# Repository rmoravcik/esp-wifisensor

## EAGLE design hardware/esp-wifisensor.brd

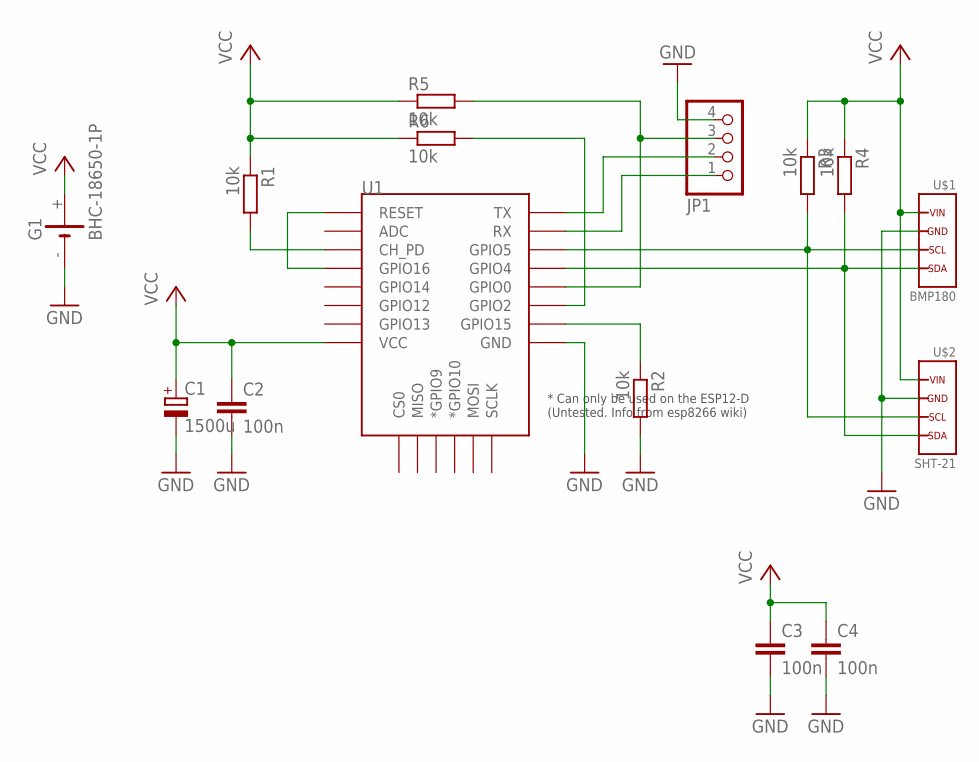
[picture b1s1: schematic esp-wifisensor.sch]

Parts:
C1: 1500u; E5-13
C2, C3, C4: 100n; C1206K
G1: BHC-18650-1P
JP1: PINHD-1X4; 1X04
R1, R2, R3, R4, R5, R6: 10k; M1206
U1: ESP12ESMD; ESP12E-SMD
U$1: BMP180
U$2: SHT-21

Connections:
GND: C1.-, C2.2, C3.2, C4.2, G1.-, JP1.4, R2.2, U1.GND, U$1.GND, U$2.GND
unnamed: U1.GPIO16, U1.RESET
unnamed: R3.2, U1.GPIO5, U$1.SCL, U$2.SCL
unnamed: R4.2, U1.GPIO4, U$1.SDA, U$2.SDA
unnamed: R2.1, U1.GPIO15
unnamed: JP1.3, R5.2, U1.GPIO0
unnamed: R1.2, U1.CH_PD
unnamed: R6.2, U1.GPIO2
unnamed: JP1.2, U1.TXD0 (TX)
unnamed: JP1.1, U1.RXD0 (RX)
VCC: C1.+, C2.1, C3.1, C4.1, G1.+, R1.1, R3.1, R4.1, R5.1, R6.1, U1.VCC, U$1.VIN, U$2.VIN

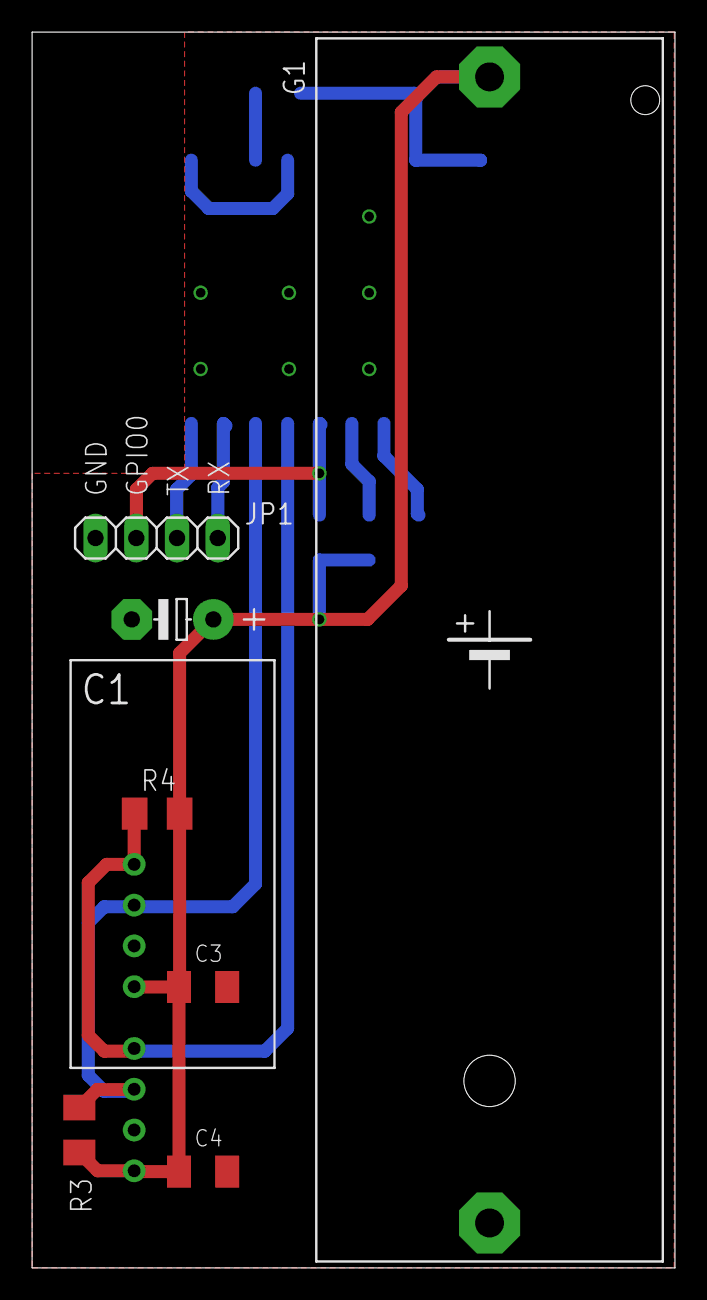
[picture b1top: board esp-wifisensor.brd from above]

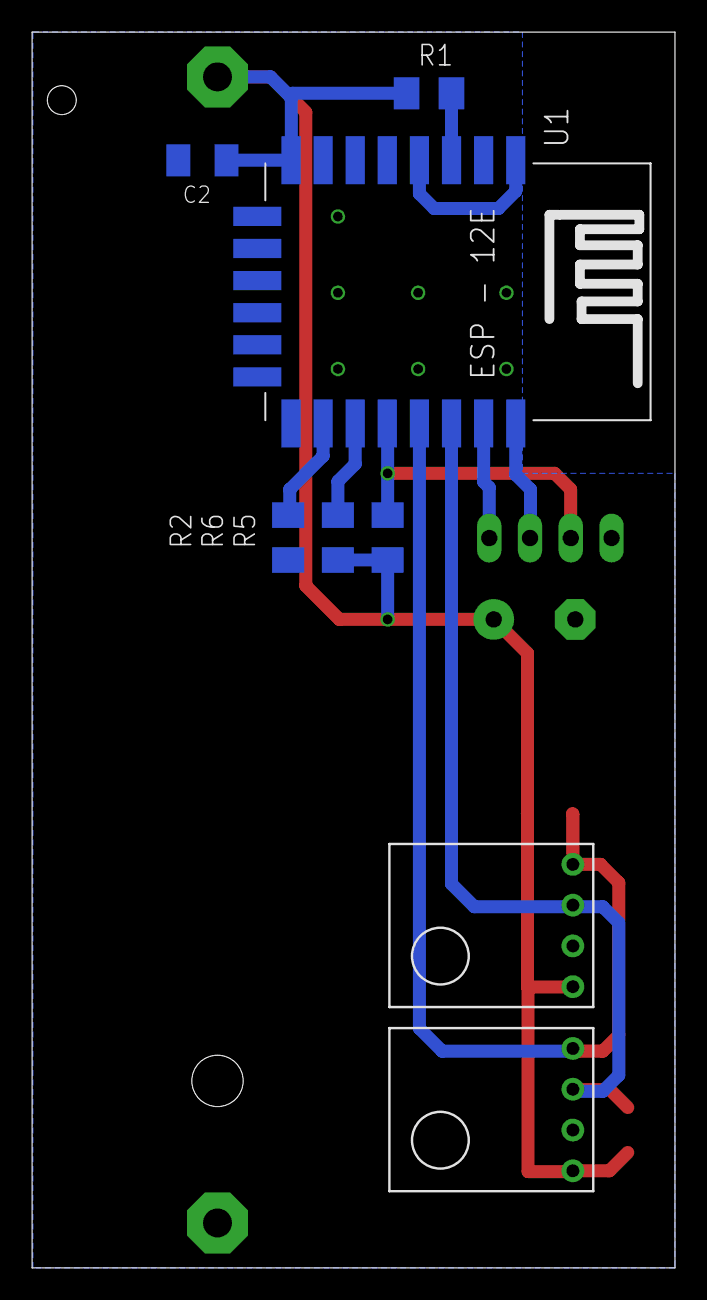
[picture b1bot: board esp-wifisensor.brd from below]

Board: 2 copper layers, 40.0 x 77.0 mm, 15 parts (8 on the bottom side), 11 nets.

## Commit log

2016-12-02 hardware: updated schematics and pcb
2016-12-03 hardware: final version of pcb
2016-12-03 hardware: minor tweak of pcb
2017-02-24 firmware: ubidots replaced by thingspeak.
2017-02-24 case: added a simple case for sensor.
2017-02-25 case: case definition translated to english
2017-03-09 case: fixed case dimensions.
2017-03-10 case: reworked sensor opennings.
2017-03-11 case: optimization for better print...
2021-04-03 Retry update of data in 1 minute is failed
